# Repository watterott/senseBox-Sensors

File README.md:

# senseBox Sensors
Sensors for senseBox Boards.

* Open-Source
* **[Documentation on learn.watterott.com](https://learn.watterott.com)**

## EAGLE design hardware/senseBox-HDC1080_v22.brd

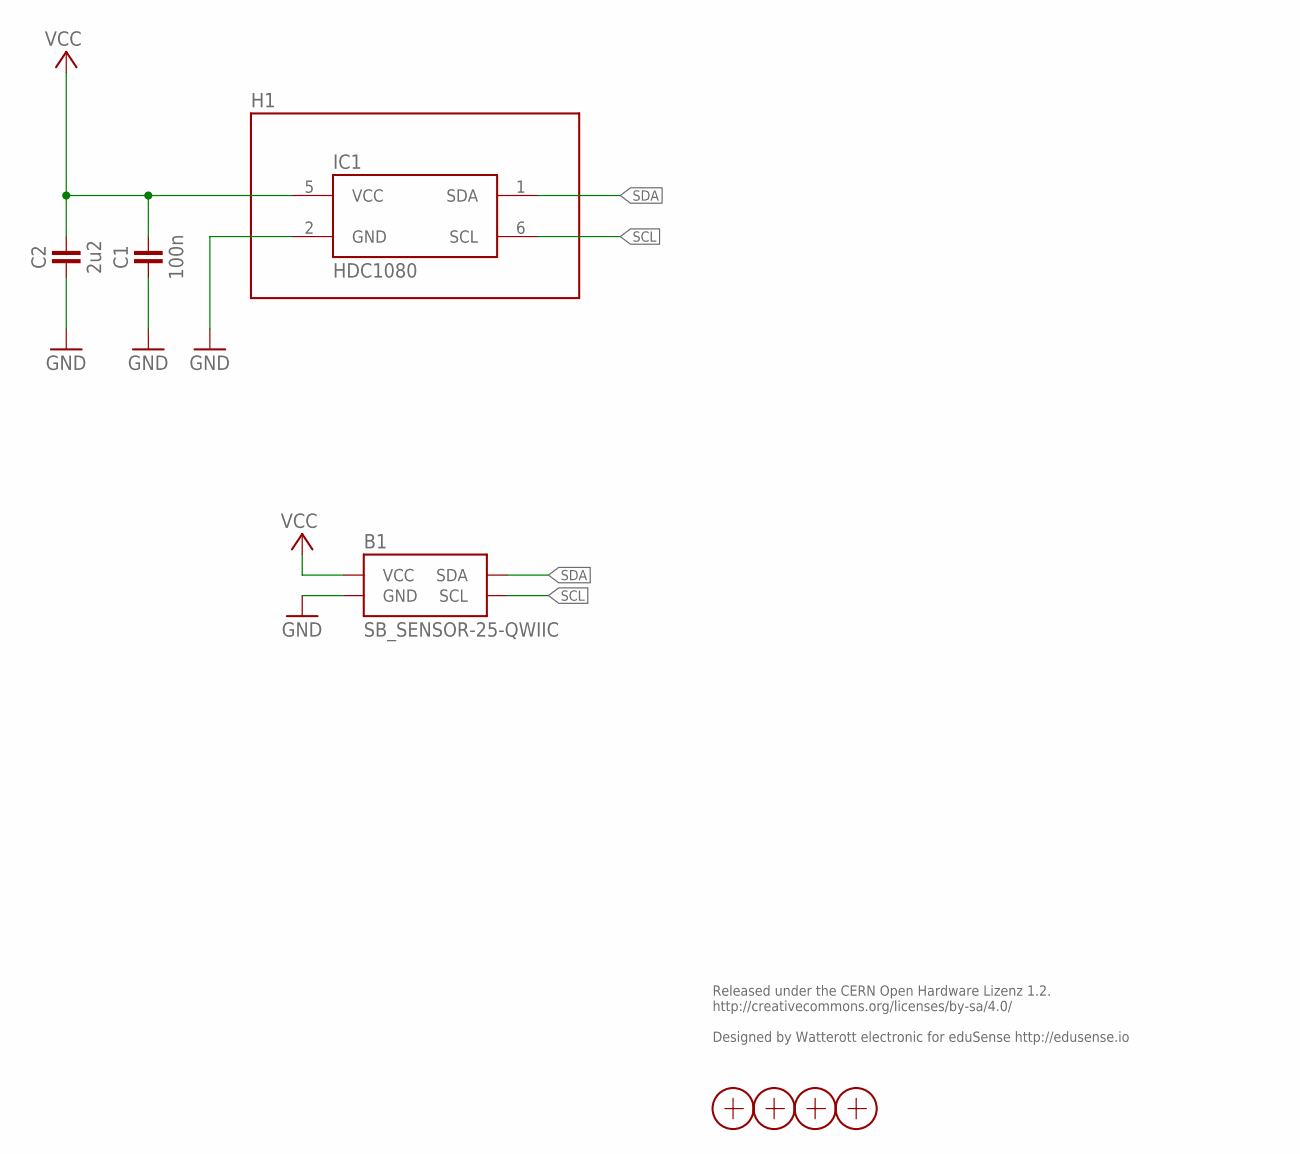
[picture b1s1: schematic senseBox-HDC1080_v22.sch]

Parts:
B1: SB_SENSOR-25-QWIIC; SB-25X25_QWIIC
C1: 100n; C0402
C2: 2u2; C0402
H1: SF2
IC1: HDC1080; WSON6
X1, X2, X3, X4: PASSER-07; PASSER_07MM

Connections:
GND: B1.GND@1 (GND), B1.GND@2 (GND), B1.GND@3 (GND), C1.1, C2.1, IC1.2 (GND)
SCL: B1.SCL@1 (SCL), B1.SCL@2 (SCL), B1.SCL@3 (SCL), IC1.6 (SCL)
SDA: B1.SDA@1 (SDA), B1.SDA@2 (SDA), B1.SDA@3 (SDA), IC1.1 (SDA)
VCC: B1.VCC@1 (VCC), B1.VCC@2 (VCC), B1.VCC@3 (VCC), C1.2, C2.2, IC1.5 (VCC)

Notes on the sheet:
Released under the CERN Open Hardware Lizenz 1.2. http://creativecommons.org/licenses/by-sa/4.0/ Designed by Watterott electronic for eduSense http://edusense.io

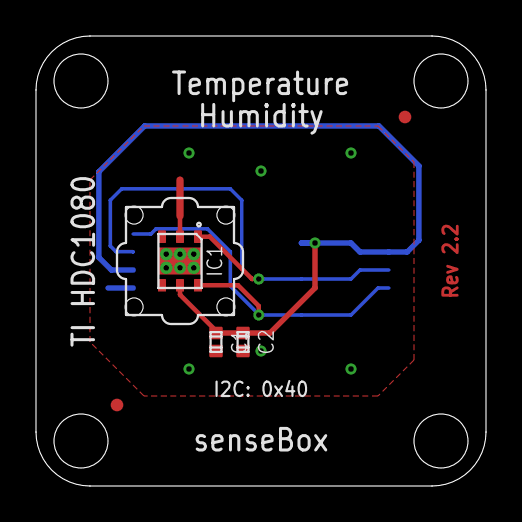
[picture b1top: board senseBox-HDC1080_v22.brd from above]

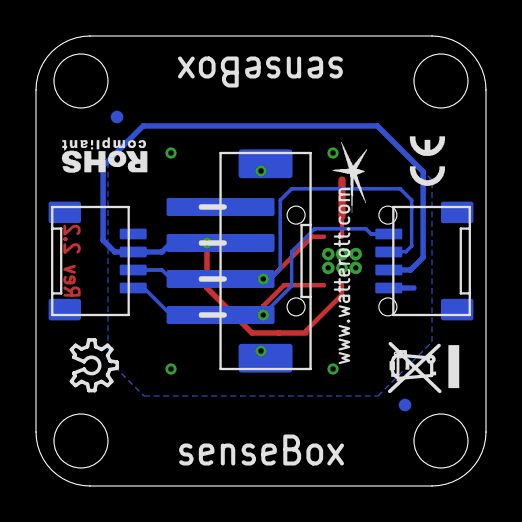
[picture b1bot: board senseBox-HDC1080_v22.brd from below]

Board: 2 copper layers, 25.0 x 25.0 mm, 9 parts (2 on the bottom side), 4 nets.

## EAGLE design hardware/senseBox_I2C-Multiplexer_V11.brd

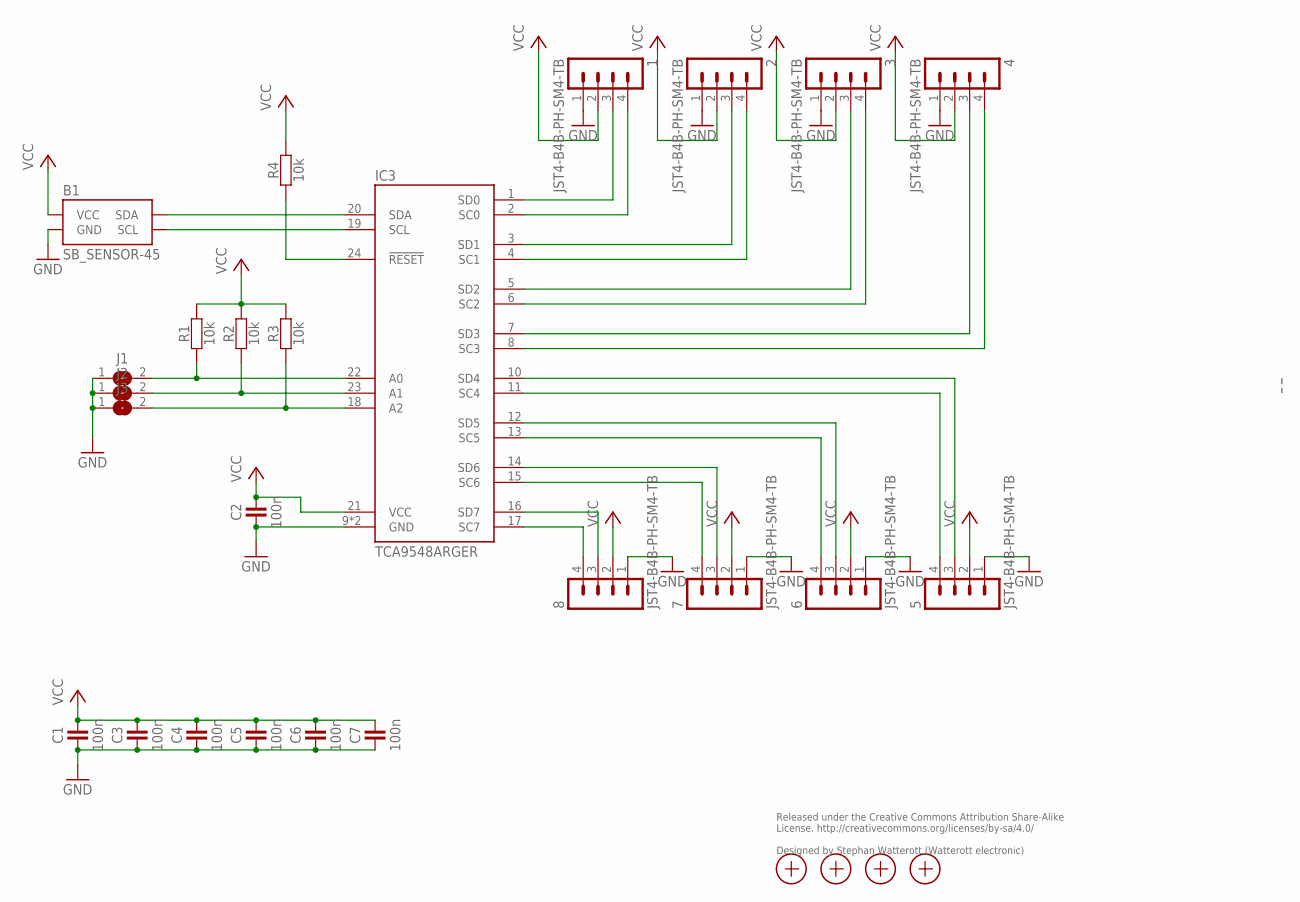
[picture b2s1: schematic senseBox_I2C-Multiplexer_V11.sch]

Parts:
1, 2, 3, 4, 5, 6, 7, 8: JST4-B4B-PH-SM4-TB; JST_B4B-PH-SM4-TB
B1: SB_SENSOR-45; SB-45X25
C1, C2, C3, C4, C5, C6, C7: 100n; C0402
IC3: TCA9548ARGER; QFN24-PAD
J1, J2, J3: JUMPER2-0402-NC; JUMPER2-0402_NC
R1, R2, R3, R4: 10k; C0402
X1, X2, X3, X4: PASSER-07; PASSER_07MM

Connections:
A0: IC3.22 (A0), J1.2, R1.1
A1: IC3.23 (A1), J2.2, R2.1
A2: IC3.18 (A2), J3.2, R3.1
GND: 1.1, 2.1, 3.1, 4.1, 5.1, 6.1, 7.1, 8.1, B1.GND, C1.1, C2.1, C3.1, C4.1, C5.1, C6.1, C7.1, IC3.9 (GND), IC3.TP (GND), J1.1, J2.1, J3.1
unnamed: 1.4, IC3.2 (SC0)
unnamed: 1.3, IC3.1 (SD0)
unnamed: 2.4, IC3.4 (SC1)
unnamed: 2.3, IC3.3 (SD1)
unnamed: 3.4, IC3.6 (SC2)
unnamed: 3.3, IC3.5 (SD2)
unnamed: 4.4, IC3.8 (SC3)
unnamed: 4.3, IC3.7 (SD3)
unnamed: 5.4, IC3.11 (SC4)
unnamed: 5.3, IC3.10 (SD4)
unnamed: 6.4, IC3.13 (SC5)
unnamed: 6.3, IC3.12 (SD5)
unnamed: 7.4, IC3.15 (SC6)
unnamed: 7.3, IC3.14 (SD6)
unnamed: 8.4, IC3.17 (SC7)
unnamed: 8.3, IC3.16 (SD7)
unnamed: B1.SDA, IC3.20 (SDA)
unnamed: IC3.24 (!RESET), R4.1
unnamed: B1.SCL, IC3.19 (SCL)
VCC: 1.2, 2.2, 3.2, 4.2, 5.2, 6.2, 7.2, 8.2, B1.VCC, C1.2, C2.2, C3.2, C4.2, C5.2, C6.2, C7.2, IC3.21 (VCC), R1.2, R2.2, R3.2, R4.2

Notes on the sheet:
Released under the Creative Commons Attribution Share-Alike License. http://creativecommons.org/licenses/by-sa/4.0/ Designed by Stephan Watterott (Watterott electronic)

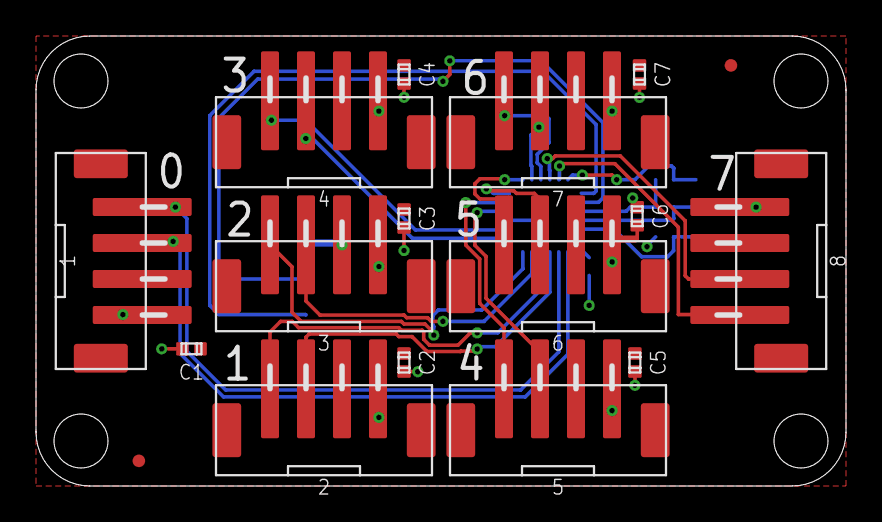
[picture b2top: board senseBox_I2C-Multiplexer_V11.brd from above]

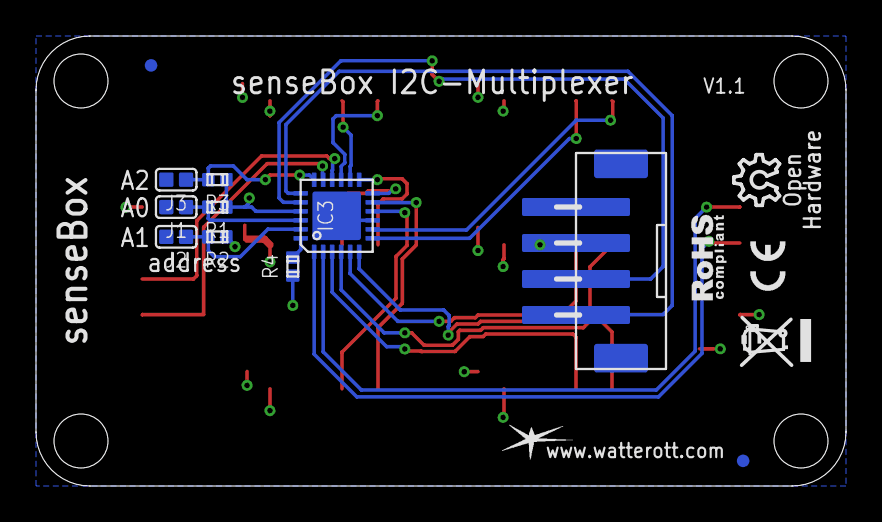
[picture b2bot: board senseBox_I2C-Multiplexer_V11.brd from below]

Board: 2 copper layers, 45.0 x 25.0 mm, 28 parts (10 on the bottom side), 24 nets.

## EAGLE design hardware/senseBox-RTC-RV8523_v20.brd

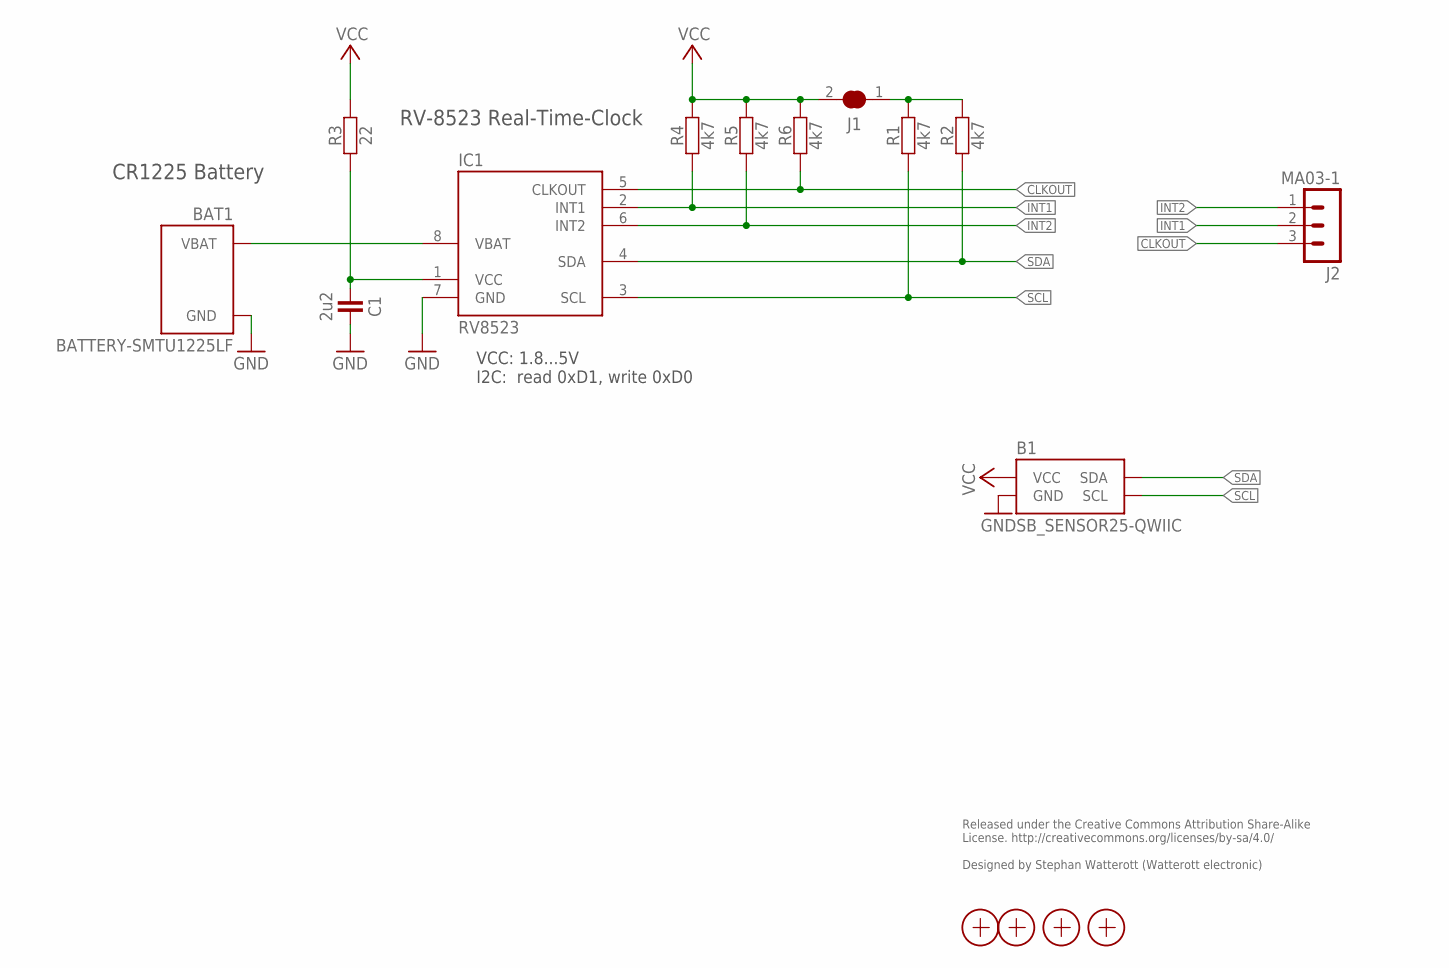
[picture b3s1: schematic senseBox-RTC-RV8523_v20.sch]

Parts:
B1: SB_SENSOR25-QWIIC; SB-25X25_QWIIC
BAT1: BATTERY-SMTU1225LF; BAT-SMTU1225LF
C1: 2u2; R0402
IC1: RV8523; RTC-C3
J1: JUMPER2
J2: MA03-1
R1, R2, R4, R5, R6: 4k7; R0402
R3: 22; R0402
X1, X2, X3, X4: PASSER-07; PASSER_07MM

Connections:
CLKOUT: IC1.5 (CLKOUT), J2.3, R6.1
GND: B1.GND, B1.GND1 (GND), B1.GND2 (GND), B1.SHLD1 (GND), B1.SHLD2 (GND), B1.SHLD3 (GND), B1.SHLD4 (GND), B1.SHLD5 (GND), B1.SHLD6 (GND), BAT1.- (GND), C1.2, IC1.7 (GND)
I2C_VCC: J1.1, R1.2, R2.2
INT1: IC1.2 (INT1), J2.2, R4.1
INT2: IC1.6 (INT2), J2.1, R5.1
RV_VCC: C1.1, IC1.1 (VCC), R3.1
SCL: B1.SCL, B1.SCL1 (SCL), B1.SCL2 (SCL), IC1.3 (SCL), R1.1
SDA: B1.SDA, B1.SDA1 (SDA), B1.SDA2 (SDA), IC1.4 (SDA), R2.1
VBAT: BAT1.+ (VBAT), IC1.8 (VBAT)
VCC: B1.VCC, B1.VCC1 (VCC), B1.VCC2 (VCC), J1.2, R3.2, R4.2, R5.2, R6.2

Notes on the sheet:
Released under the Creative Commons Attribution Share-Alike License. http://creativecommons.org/licenses/by-sa/4.0/ Designed by Stephan Watterott (Watterott electronic)
VCC: 1.8...5V I2C: read 0xD1, write 0xD0
RV-8523 Real-Time-Clock
CR1225 Battery

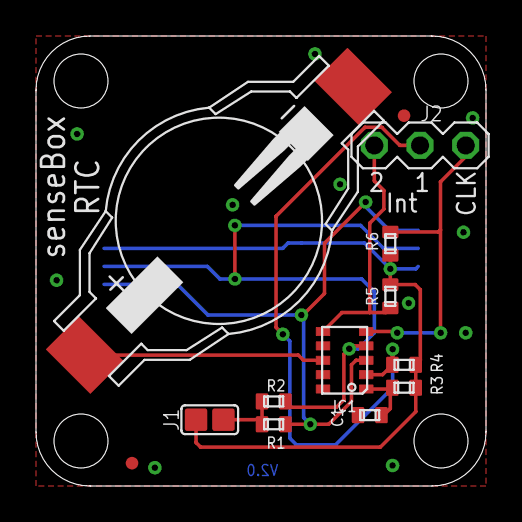
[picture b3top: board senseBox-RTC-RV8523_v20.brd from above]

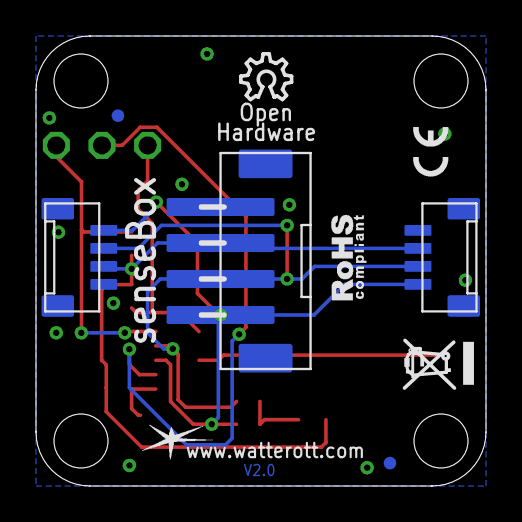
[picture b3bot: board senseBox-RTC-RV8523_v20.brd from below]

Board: 2 copper layers, 25.0 x 25.0 mm, 16 parts (2 on the bottom side), 10 nets.

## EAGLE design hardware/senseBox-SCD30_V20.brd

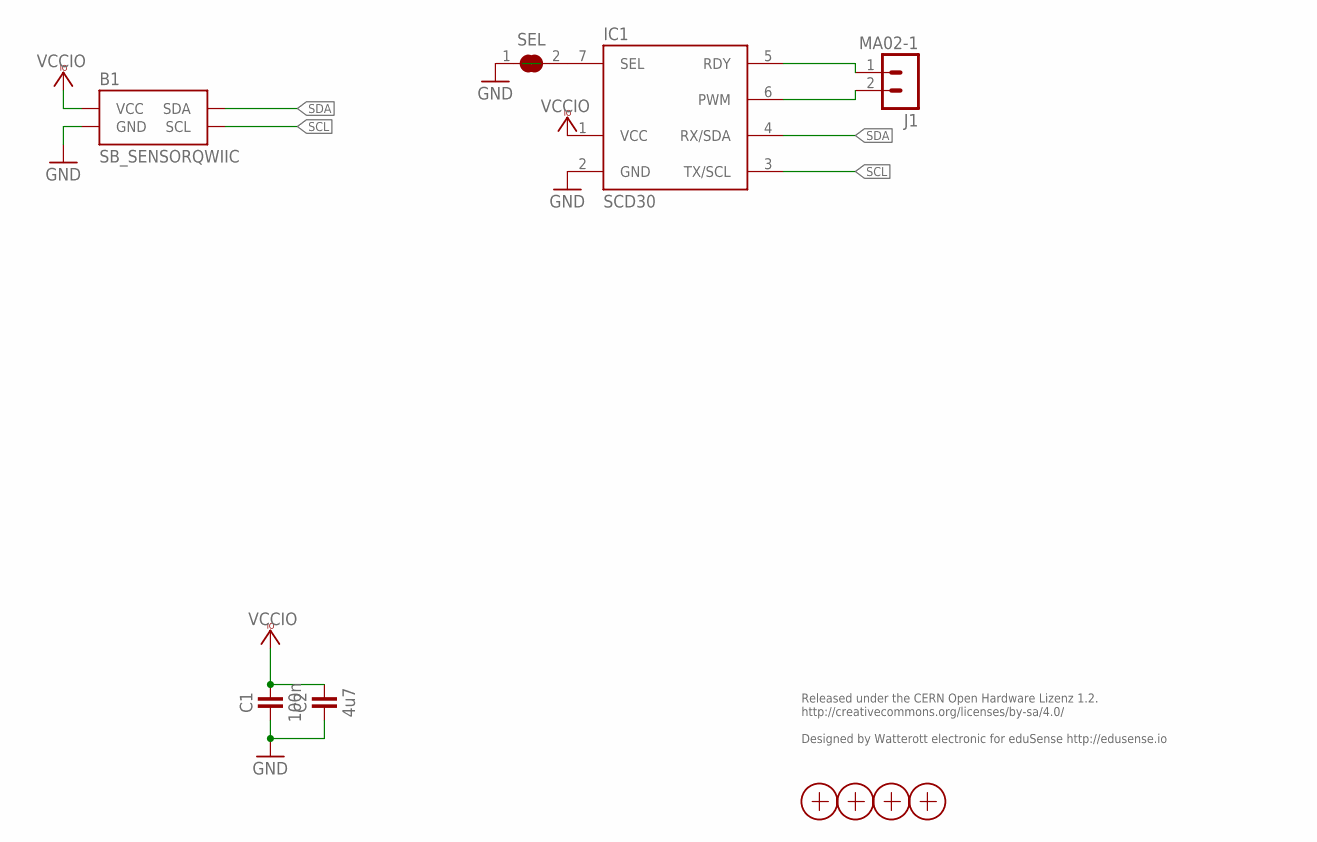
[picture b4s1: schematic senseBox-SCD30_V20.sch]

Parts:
B1: SB_SENSORQWIIC; SB-45X25_QWIIC
C1: 100n; C0402
C2: 4u7; C0402
IC1: SCD30
J1: MA02-1
SEL: JUMPER2-0402-NC; JUMPER2-0402_NC
X1, X2, X3, X4: PASSER-07; PASSER_07MM

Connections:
GND: B1.GND, B1.GND1 (GND), B1.GND2 (GND), B1.SHLD1 (GND), B1.SHLD2 (GND), B1.SHLD3 (GND), B1.SHLD4 (GND), B1.SHLD5 (GND), B1.SHLD6 (GND), C1.1, C2.1, IC1.2 (GND), SEL.1
unnamed: IC1.6 (PWM), J1.2
unnamed: IC1.7 (SEL), SEL.2
RDY: IC1.5 (RDY), J1.1
SCL: B1.SCL, B1.SCL1 (SCL), B1.SCL2 (SCL), IC1.3 (TX/SCL)
SDA: B1.SDA, B1.SDA1 (SDA), B1.SDA2 (SDA), IC1.4 (RX/SDA)
VCCIO: B1.VCC, B1.VCC1 (VCC), B1.VCC2 (VCC), C1.2, C2.2, IC1.1 (VCC)

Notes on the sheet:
Released under the CERN Open Hardware Lizenz 1.2. http://creativecommons.org/licenses/by-sa/4.0/ Designed by Watterott electronic for eduSense http://edusense.io

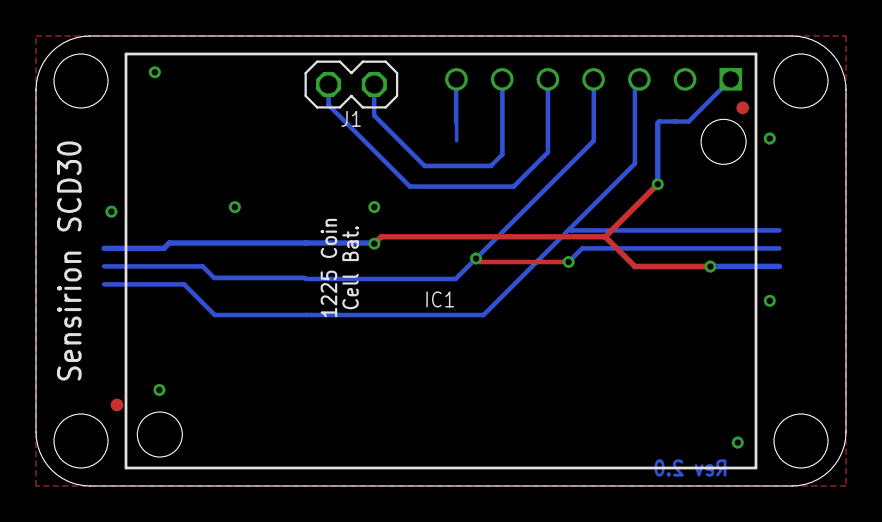
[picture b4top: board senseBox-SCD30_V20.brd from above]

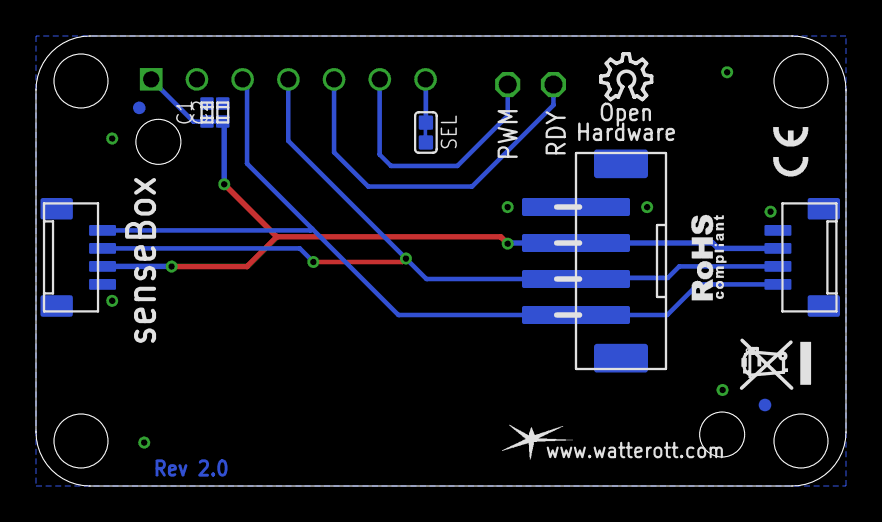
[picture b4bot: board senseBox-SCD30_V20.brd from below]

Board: 2 copper layers, 45.0 x 25.0 mm, 10 parts (5 on the bottom side), 7 nets.

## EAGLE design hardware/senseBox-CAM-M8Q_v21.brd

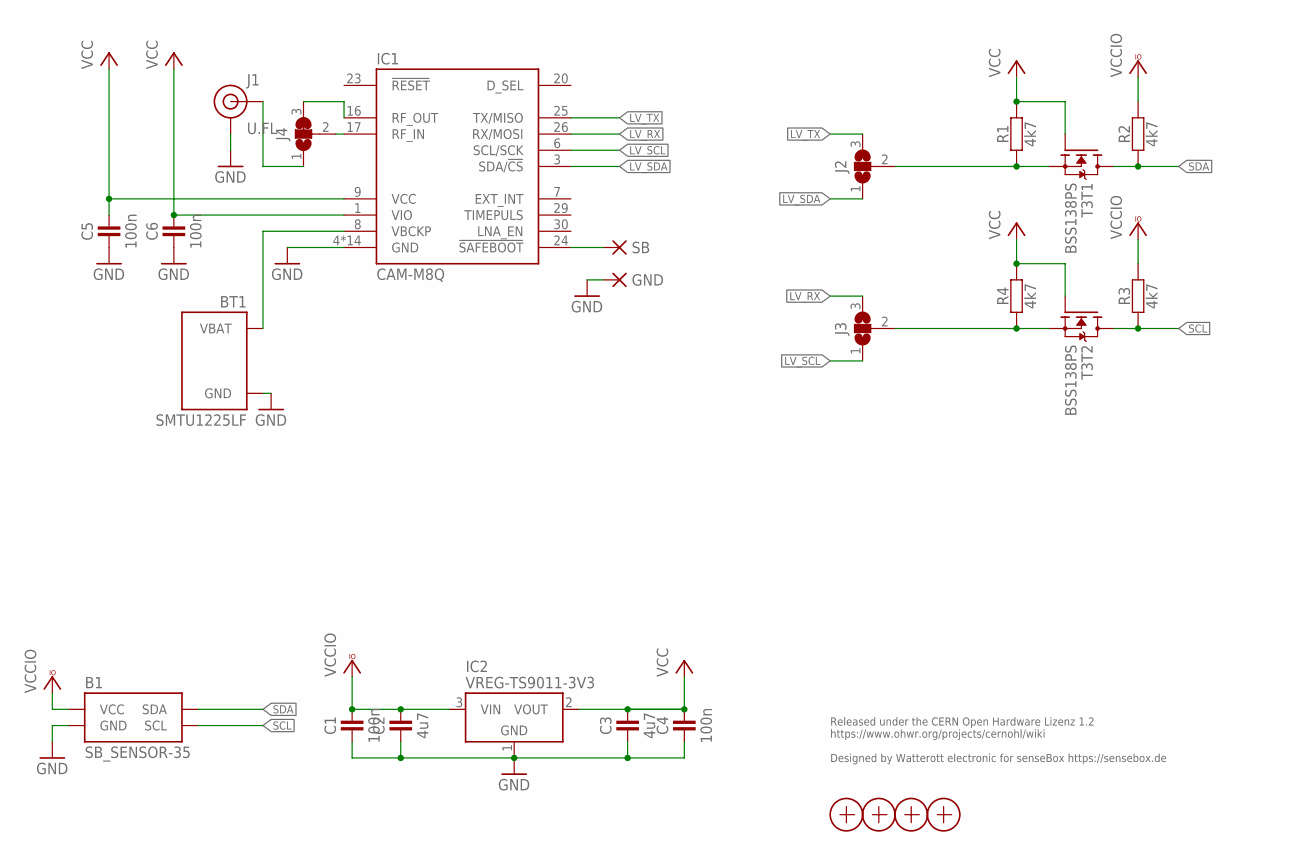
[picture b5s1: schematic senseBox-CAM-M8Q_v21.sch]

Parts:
B1: SB_SENSOR-35; SB-35X25
BT1: SMTU1225LF; BAT-SMTU1225LF
C1, C4, C5, C6: 100n; C0402
C2, C3: 4u7; C0402
GND: PAD-1.27X1.27_NC
IC1: CAM-M8Q
IC2: VREG-TS9011-3V3; SOT23
J1: U.FL
J2, J3: JUMPER3-0603-NC; JUMPER3-0603_NC
J4: JUMPER3-0603
R1, R2, R3, R4: 4k7; C0402
SB: PAD-1.27X1.27_NC
T3: BSS138PS; SOT363
X1, X2, X3, X4: PASSER-07; PASSER_07MM

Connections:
GND: B1.GND, BT1.- (GND), C1.1, C2.1, C3.1, C4.1, C5.1, C6.1, GND.1, IC1.4 (GND), IC1.5 (GND), IC1.10 (GND), IC1.11 (GND), IC1.12 (GND), IC1.13 (GND), IC1.14 (GND), IC1.15 (GND), IC1.18 (GND), IC1.19 (GND), IC1.21 (GND), IC1.22 (GND), IC1.27 (GND), IC1.31 (GND), IC2.1 (GND), J1.1 (GND), J1.2 (GND)
LV_RX: IC1.26 (RX/MOSI), J3.3
LV_SCL: IC1.6 (SCL/SCK), J3.1
LV_SDA: IC1.3 (SDA/!CS), J2.1
LV_TX: IC1.25 (TX/MISO), J2.3
unnamed: J2.2, R1.1, T3.1 (S)
unnamed: J3.2, R4.1, T3.4 (S)
unnamed: J1.FEED (SIGNAL), J4.1
RFIN: IC1.17 (RF_IN), J4.2
RFOUT: IC1.16 (RF_OUT), J4.3
SB: IC1.24 (!SAFEBOOT), SB.1
SCL: B1.SCL, R3.1, T3.3 (D)
SDA: B1.SDA, R2.1, T3.6 (D)
VBAT: BT1.+ (VBAT), IC1.8 (VBCKP)
VCC: C3.2, C4.2, C5.2, C6.2, IC1.1 (VIO), IC1.9 (VCC), IC2.2 (VOUT), R1.2, R4.2, T3.2 (G), T3.5 (G)
VCCIO: B1.VCC, C1.2, C2.2, IC2.3 (VIN), R2.2, R3.2

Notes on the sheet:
Released under the CERN Open Hardware Lizenz 1.2 https://www.ohwr.org/projects/cernohl/wiki Designed by Watterott electronic for senseBox https://sensebox.de

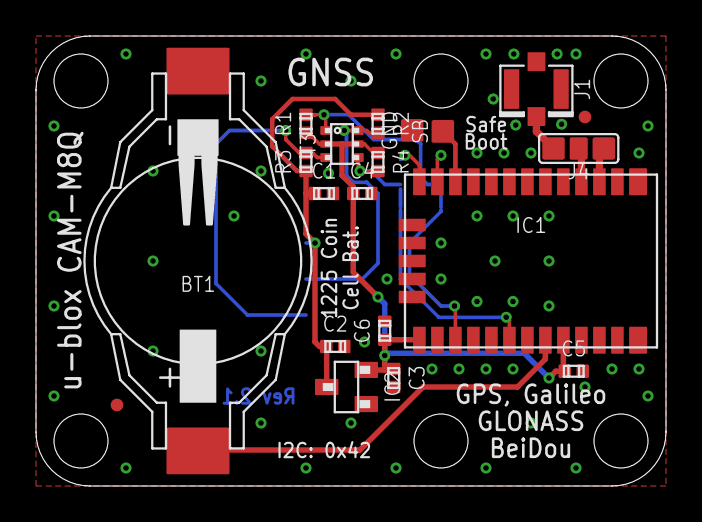
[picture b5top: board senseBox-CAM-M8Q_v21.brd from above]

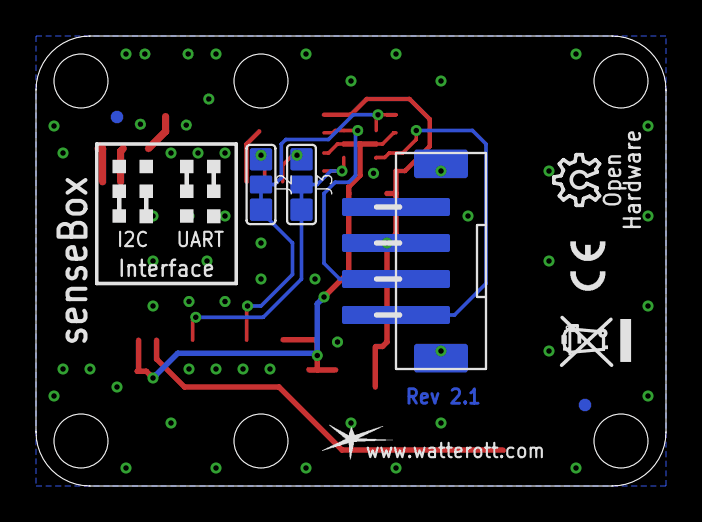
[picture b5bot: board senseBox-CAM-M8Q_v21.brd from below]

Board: 2 copper layers, 35.0 x 25.0 mm, 25 parts (4 on the bottom side), 16 nets.

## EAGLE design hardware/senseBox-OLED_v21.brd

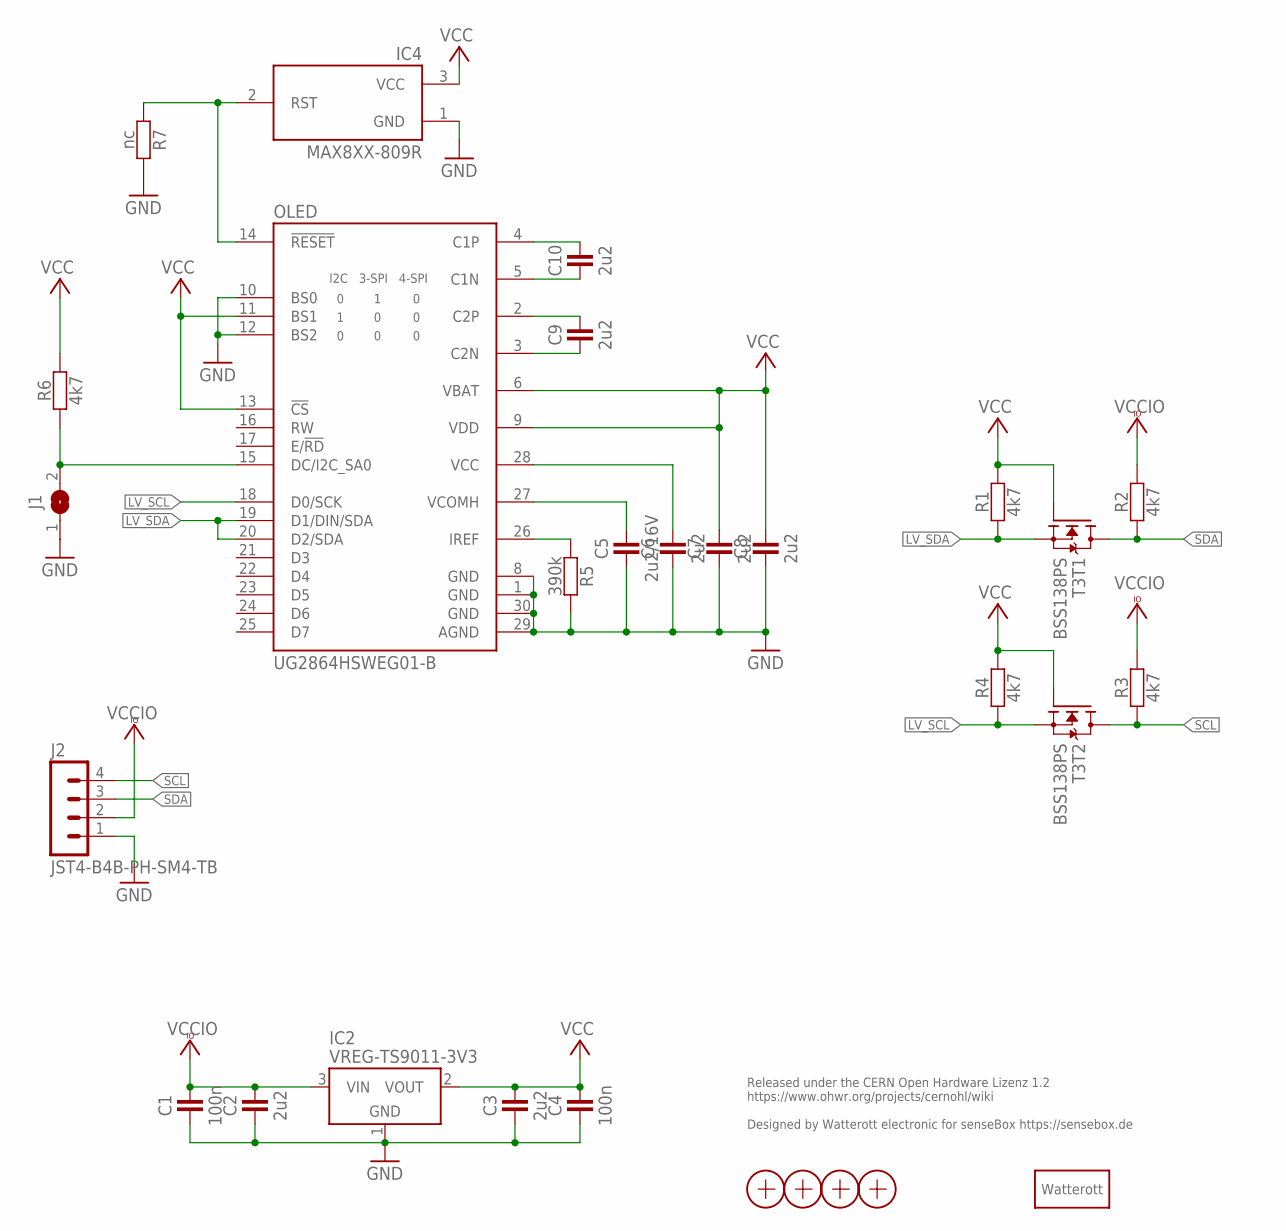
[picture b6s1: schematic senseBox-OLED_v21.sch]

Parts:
C1, C4: 100n; C0402
C2, C3, C6, C7, C8, C9, C10: 2u2; C0402
C5: 2u2/16V; C0402
IC2: VREG-TS9011-3V3; SOT23
IC4: MAX8XX-809R; SOT23
J1: JUMPER2-0402-NC; JUMPER2-0402_NC
J2: JST4-B4B-PH-SM4-TB; JST_B4B-PH-SM4-TB
LOGO1: LOGO_SPARK-2; SPARK_2MM
OLED: UG2864HSWEG01-B; UG2864HSWEG01_BOT
R1, R2, R3, R4, R6: 4k7; C0402
R5: 390k; C0402
R7: nc; C0402
T3: BSS138PS; SOT363
X1, X2, X3, X4: PASSER-07; PASSER_07MM

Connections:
C1N: C10.1, OLED.5 (C1N)
C1P: C10.2, OLED.4 (C1P)
C2N: C9.1, OLED.3 (C2N)
C2P: C9.2, OLED.2 (C2P)
GND: C1.1, C2.1, C3.1, C4.1, C5.1, C6.1, C7.1, C8.1, IC2.1 (GND), IC4.1 (GND), J1.1, J2.1, OLED.1 (GND), OLED.8 (GND), OLED.10 (BS0), OLED.12 (BS2), OLED.29 (AGND), OLED.30 (GND), R5.2, R7.2
IREF: OLED.26 (IREF), R5.1
LV_SCL: OLED.18 (D0/SCK), R4.1, T3.4 (S)
LV_SDA: OLED.19 (D1/DIN/SDA), OLED.20 (D2/SDA), R1.1, T3.1 (S)
RST: IC4.2 (RST), OLED.14 (!RESET), R7.1
SA0: J1.2, OLED.15 (DC/I2C_SA0), R6.1
SCL: J2.4, R3.1, T3.3 (D)
SDA: J2.3, R2.1, T3.6 (D)
VC: C6.2, OLED.28 (VCC)
VCC: C3.2, C4.2, C7.2, C8.2, IC2.2 (VOUT), IC4.3 (VCC), OLED.6 (VBAT), OLED.9 (VDD), OLED.11 (BS1), OLED.13 (!CS), R1.2, R4.2, R6.2, T3.2 (G), T3.5 (G)
VCCIO: C1.2, C2.2, IC2.3 (VIN), J2.2, R2.2, R3.2
VCH: C5.2, OLED.27 (VCOMH)

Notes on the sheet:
Released under the CERN Open Hardware Lizenz 1.2 https://www.ohwr.org/projects/cernohl/wiki Designed by Watterott electronic for senseBox https://sensebox.de

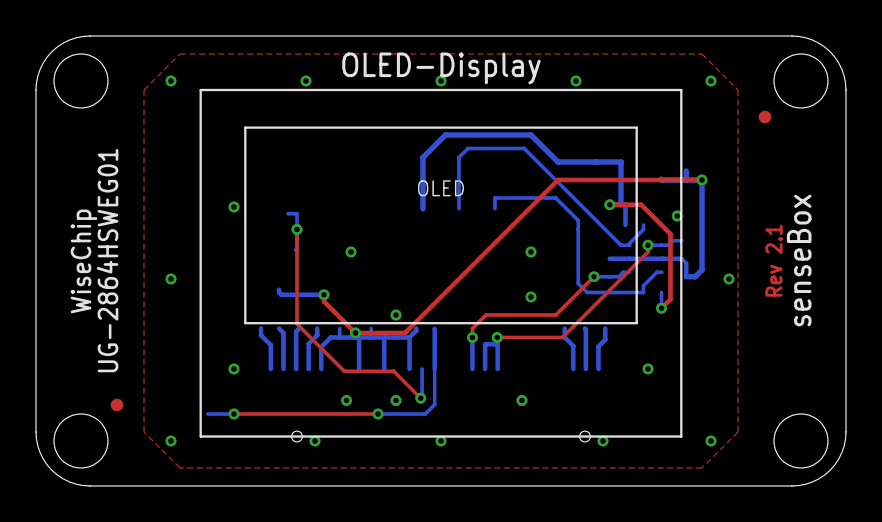
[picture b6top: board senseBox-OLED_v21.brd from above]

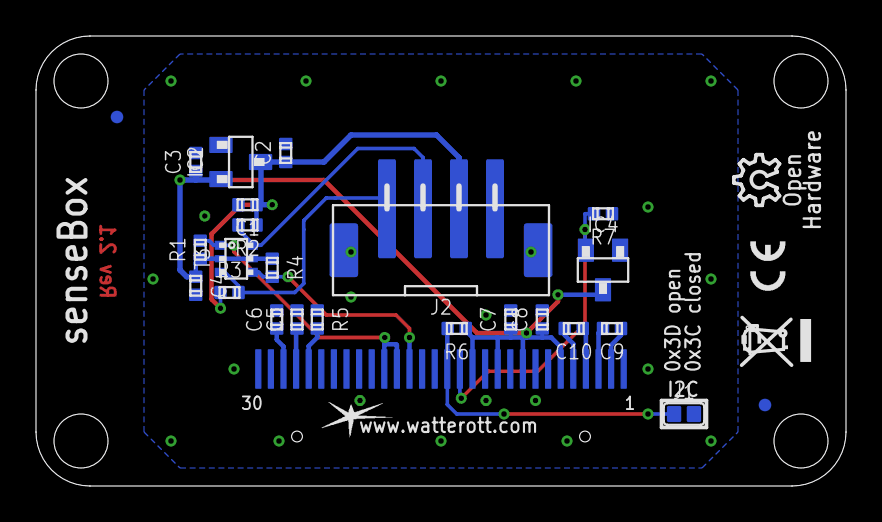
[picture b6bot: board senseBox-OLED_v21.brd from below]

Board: 2 copper layers, 45.0 x 25.0 mm, 28 parts (25 on the bottom side), 16 nets.

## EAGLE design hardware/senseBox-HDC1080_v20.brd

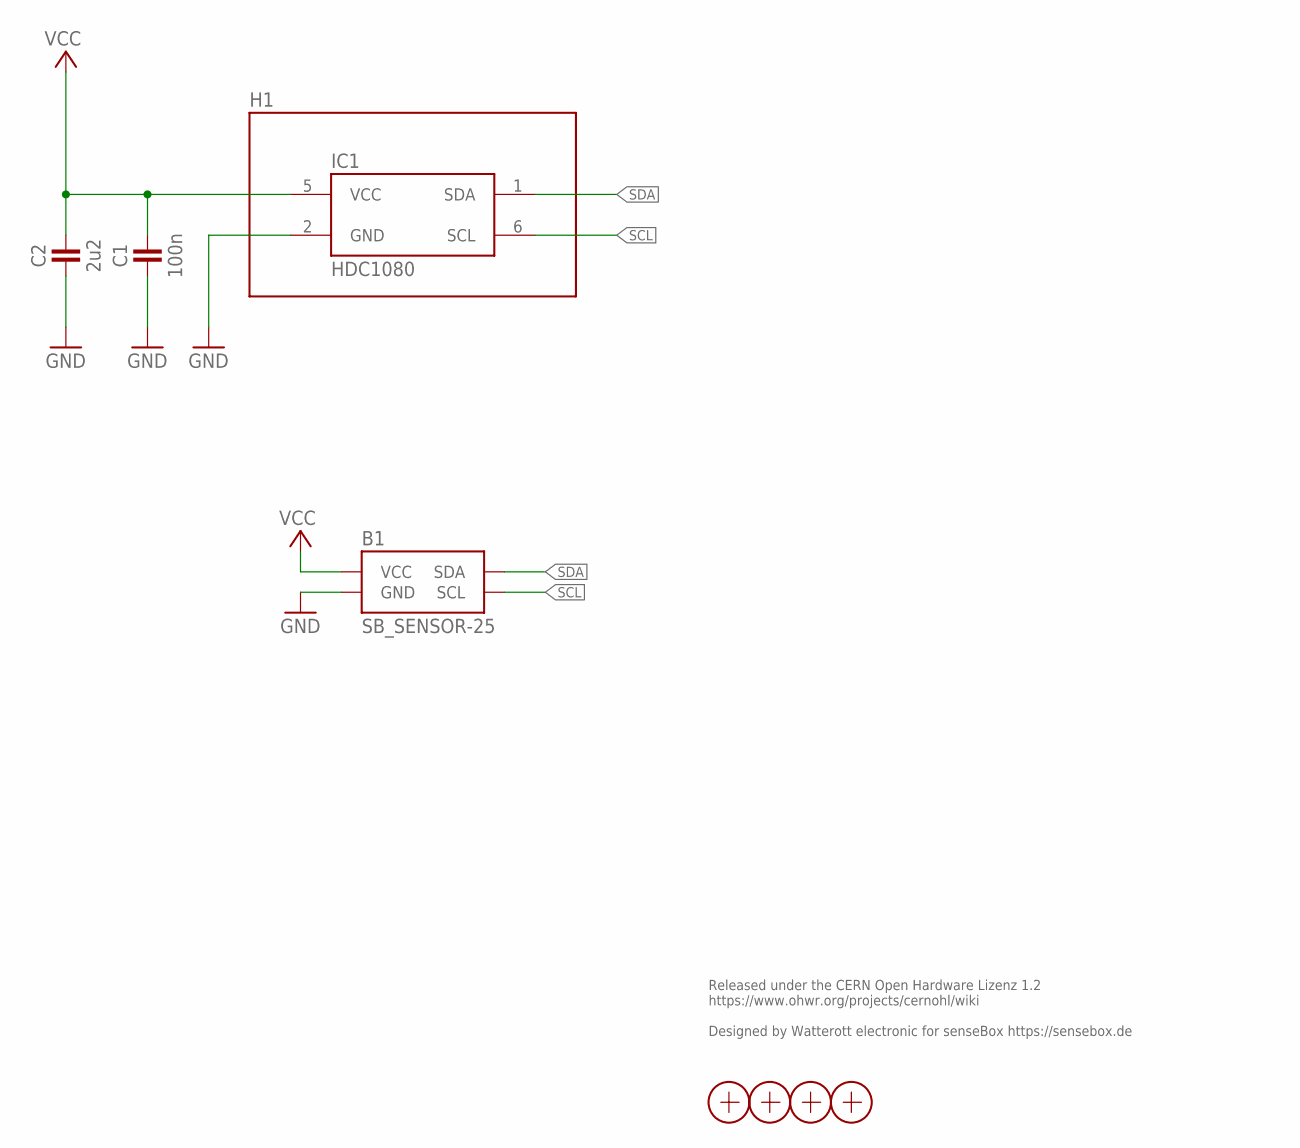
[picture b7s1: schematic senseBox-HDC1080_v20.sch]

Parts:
B1: SB_SENSOR-25; SB-25X25
C1: 100n; C0402
C2: 2u2; C0402
H1: SF2
IC1: HDC1080; WSON6
X1, X2, X3, X4: PASSER-07; PASSER_07MM

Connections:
GND: B1.GND, C1.1, C2.1, IC1.2 (GND)
SCL: B1.SCL, IC1.6 (SCL)
SDA: B1.SDA, IC1.1 (SDA)
VCC: B1.VCC, C1.2, C2.2, IC1.5 (VCC)

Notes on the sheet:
Released under the CERN Open Hardware Lizenz 1.2 https://www.ohwr.org/projects/cernohl/wiki Designed by Watterott electronic for senseBox https://sensebox.de
